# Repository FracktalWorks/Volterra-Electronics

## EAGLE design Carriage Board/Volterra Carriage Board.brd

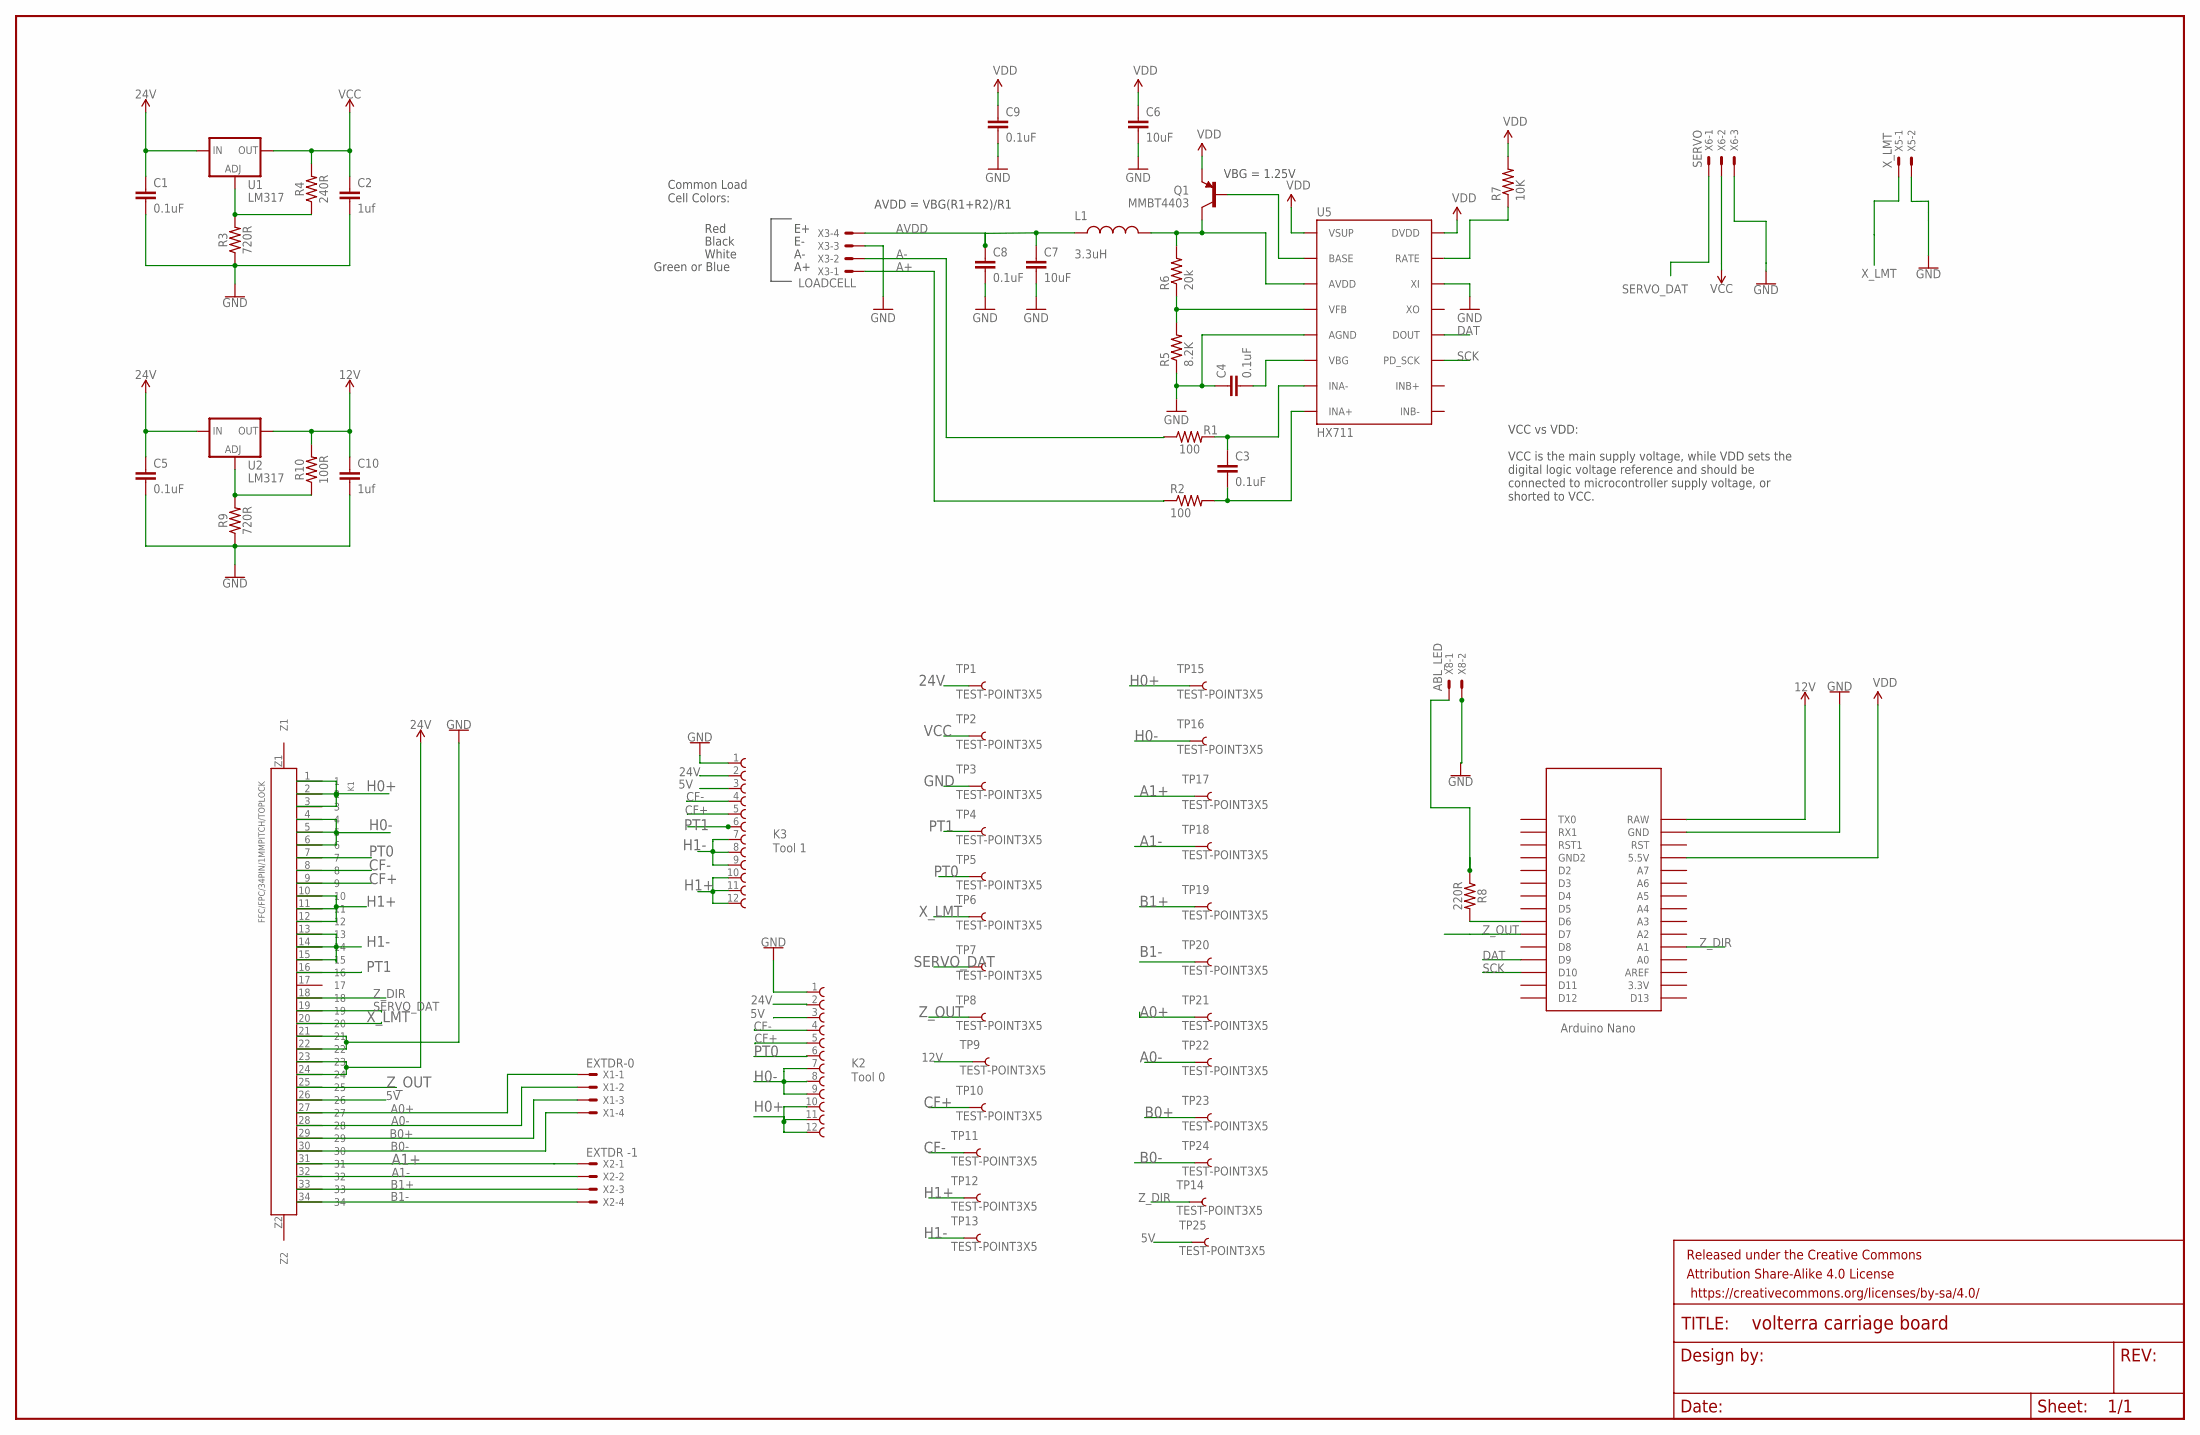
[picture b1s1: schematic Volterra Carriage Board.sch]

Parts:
C1, C5: 0.1uF; 0603
C2, C10: 1uf; 0603
C3, C4, C8, C9: 0.1uF; 0603-CAP
C6, C7: 10uF; 1210
FRAME1: FRAME-LEDGER; CREATIVE_COMMONS
K1: FFC/FPC/34PIN/1MMPITCH/TOPLOCK; 34PIN/1MMPITCH/FFC/FPC
K2: Tool 0; 68611214122
K3: Tool 1; 68611214122
L1: 3.3uH; 0805
Q1: MMBT4403; SOT23-3
R1, R2: 100; 0603-RES
R3, R9: 720R; 0603
R4: 240R; 0603
R5: 8.2K; 0603-RES
R6: 20k; 0603-RES
R7: 10K; 0603-RES
R8: 220R; 0603
R10: 100R; 0603
TP1, TP2, TP3, TP4, TP5, TP6, TP7, TP8, TP9, TP10, TP11, TP12, TP13, TP14, TP15, TP16, TP17, TP18, TP19, TP20, TP21, TP22, TP23, TP24, TP25: TEST-POINT3X5; PAD.03X.05
U1, U2: LM317; SOT223
U5: HX711; SO16
U$1: NANO
X1: EXTDR-0; JST-XH-04-PACKAGE-LONG-PAD
X2: EXTDR -1; JST-XH-04-PACKAGE-LONG-PAD
X3: LOADCELL; JST-XH-04-PACKAGE-LONG-PAD
X5: X_LMT; JST-XH-02-PACKAGE-LONG-PAD
X6: SERVO; JST-XH-03-PACKAGE-LONG-PAD
X8: ABL_LED; JST-XH-02-PACKAGE-LONG-PAD

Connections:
5V: K1.26, K2.3, K3.3, TP25.P$1
12V: C10.1, R10.2, TP9.P$1, U2.2 (OUT), U$1.RAW
24V: C1.1, C5.1, K1.23, K1.24, K2.2, K3.2, TP1.P$1, U1.3 (IN), U2.3 (IN)
A0+: K1.27, TP21.P$1, X1.1
A0-: K1.28, TP22.P$1, X1.2
A1+: K1.31, TP17.P$1, X2.1
A1-: K1.32, TP18.P$1, X2.2
A+: R2.1, X3.1
A-: R1.1, X3.2
ADJ: R3.2, R4.1, U1.1 (ADJ)
ADJ1: R9.2, R10.1, U2.1 (ADJ)
AVDD: C7.1, C8.1, L1.1, X3.4
B0+: K1.29, TP23.P$1, X1.3
B0-: K1.30, TP24.P$1, X1.4
B1+: K1.33, TP19.P$1, X2.3
B1-: K1.34, TP20.P$1, X2.4
CF+: K1.9, K2.5, K3.5, TP10.P$1
CF-: K1.8, K2.4, K3.4, TP11.P$1
DAT: U5.12 (DOUT), U$1.D9
GND: C1.2, C2.2, C4.1, C5.2, C6.2, C7.2, C8.2, C9.2, C10.2, K1.21, K1.22, K2.1, K3.1, R3.1, R5.1, R9.1, TP3.P$1, U5.5 (AGND), U5.14 (XI), U$1.GND, X3.3, X5.2, X6.3, X8.2
H0+: K1.1, K1.2, K1.3, K2.10, K2.11, K2.12, TP15.P$1
H0-: K1.4, K1.5, K1.6, K2.7, K2.8, K2.9, TP16.P$1
H1+: K1.10, K1.11, K1.12, K3.10, K3.11, K3.12, TP12.P$1
H1-: K1.13, K1.14, K1.15, K3.7, K3.8, K3.9, TP13.P$1
unnamed: R8.2, U$1.D6
unnamed: R7.1, U5.15 (RATE)
unnamed: C3.1, R1.2, U5.7 (INA-)
unnamed: Q1.1 (B), U5.2 (BASE)
unnamed: L1.2, Q1.3 (C), R6.2, U5.3 (AVDD)
unnamed: R5.2, R6.1, U5.4 (VFB)
unnamed: C4.2, U5.6 (VBG)
unnamed: C3.2, R2.2, U5.8 (INA+)
unnamed: R8.1, X8.1
PT0: K1.7, K2.6, TP5.P$1
PT1: K1.16, K3.6, TP4.P$1
SCK: U5.11 (PD_SCK), U$1.D10
SERVO_DAT: K1.19, TP7.P$1, X6.1
VCC: C2.1, R4.2, TP2.P$1, U1.2 (OUT), X6.2
VDD: C6.1, C9.1, Q1.2 (E), R7.2, U5.1 (VSUP), U5.16 (DVDD), U$1.5V (5.5V)
X_LMT: K1.20, TP6.P$1, X5.1
Z_DIR: K1.18, TP14.P$1, U$1.A1
Z_OUT: K1.25, TP8.P$1, U$1.D7

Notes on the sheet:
VBG = 1.25V
AVDD = VBG(R1+R2)/R1
Red
Black
White
Green or Blue
Common Load Cell Colors:
VCC vs VDD: VCC is the main supply voltage, while VDD sets the digital logic voltage reference and should be connected to microcontroller supply voltage, or shorted to VCC.

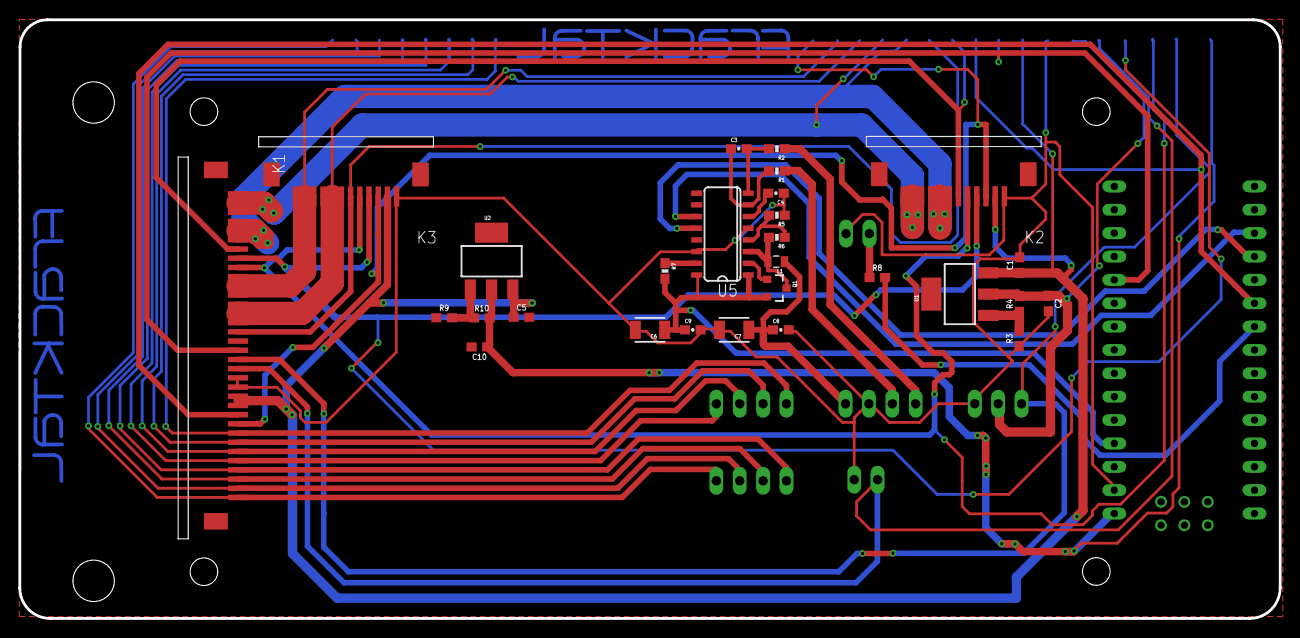
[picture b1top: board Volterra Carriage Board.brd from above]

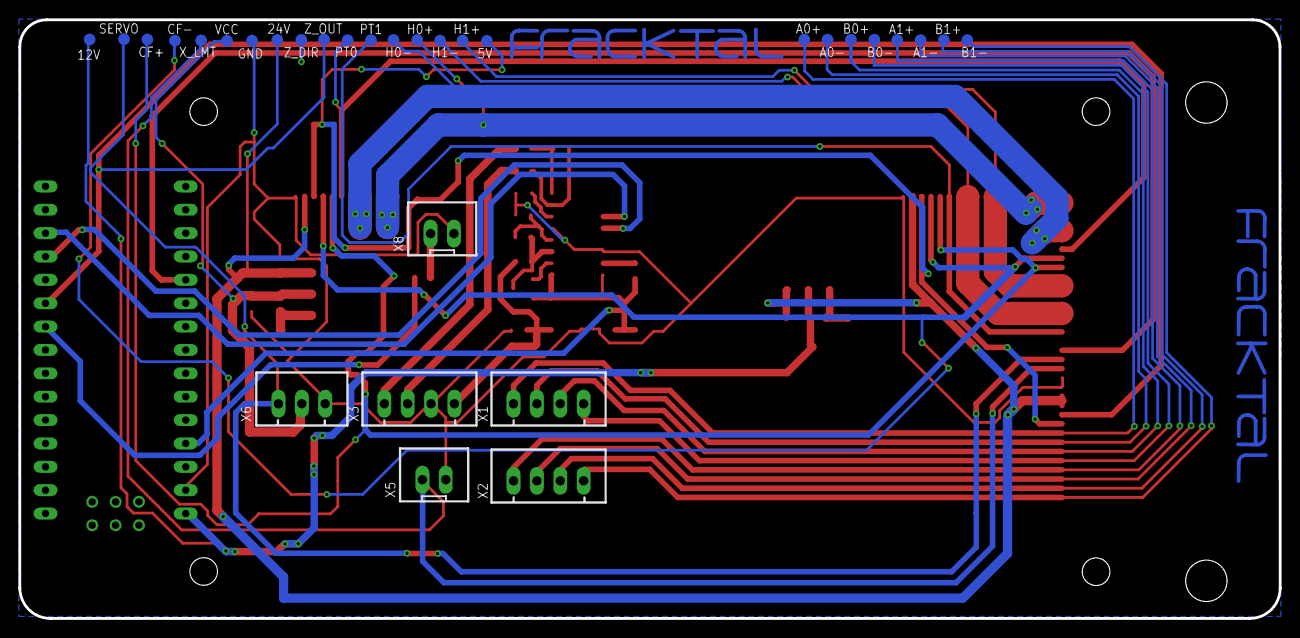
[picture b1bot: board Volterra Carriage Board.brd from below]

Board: 2 copper layers, 137.0 x 65.1 mm, 63 parts (33 on the bottom side), 42 nets.

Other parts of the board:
U$2, U$3: FRACKTALLOGO

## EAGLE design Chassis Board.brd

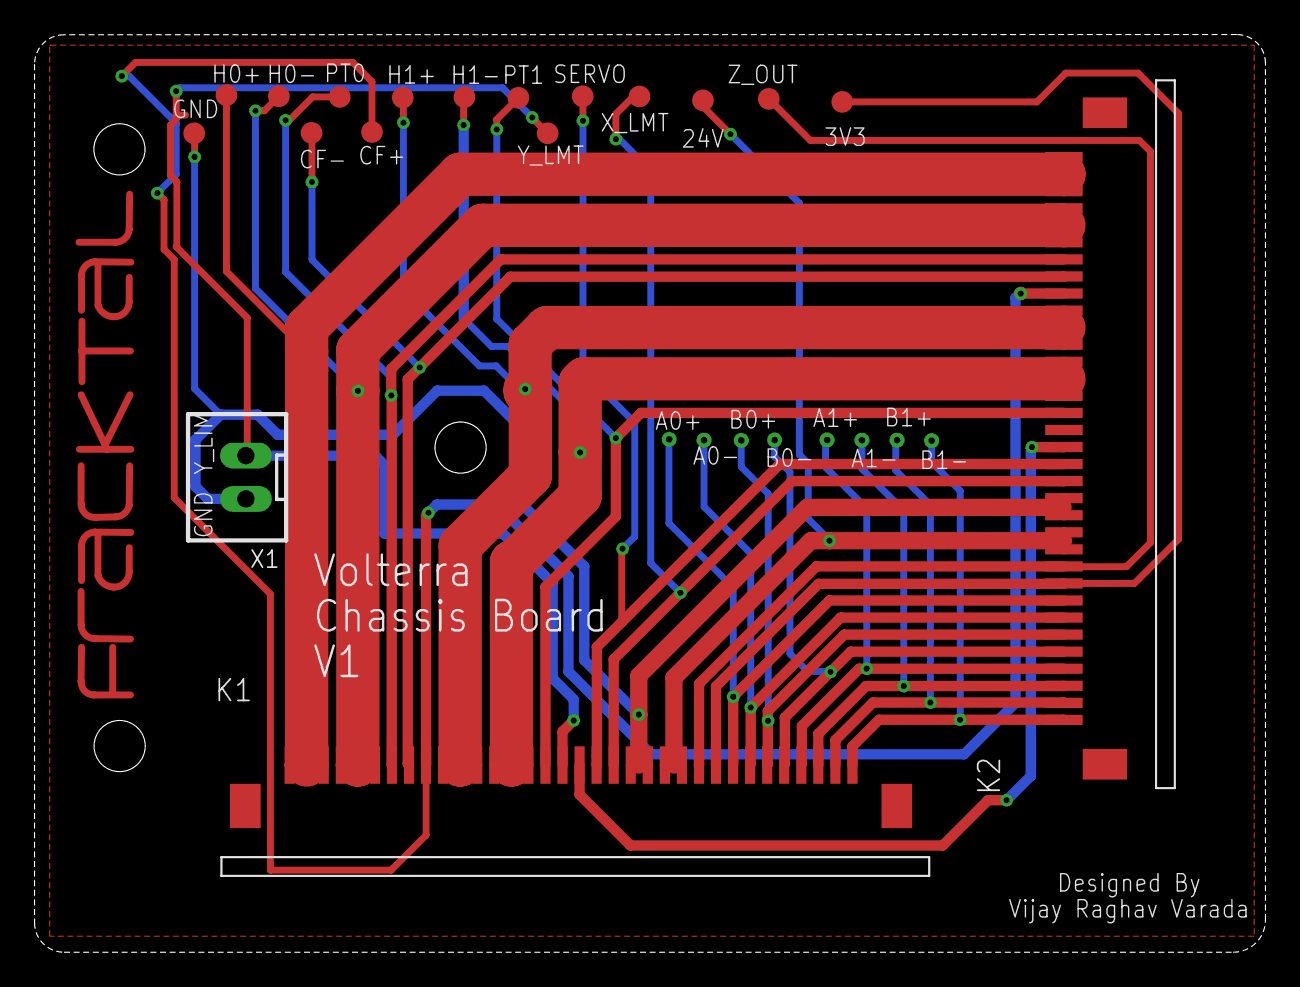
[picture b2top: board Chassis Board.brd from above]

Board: 2 copper layers, 72.2 x 53.8 mm, 27 parts (0 on the bottom side), 24 nets.

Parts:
K1, K2: FFC/FPC/34PIN/1MMPITCH/TOPLOCK; 34PIN/1MMPITCH/FFC/FPC
TP1, TP2, TP3, TP4, TP5, TP6, TP7, TP8, TP9, TP10, TP11, TP12, TP13, TP14, TP23: TEST-POINT3X5; PAD.03X.05
TP15, TP16, TP17, TP18, TP19, TP20, TP21, TP22: TEST-POINTTP_15TH_THRU; TP_15TH
U$1: FRACKTALLOGO
X1: Y_LMT; JST-XH-02-PACKAGE-LONG-PAD

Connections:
3V3: K1.26, K2.9, TP9.P$1
24V: K1.23, K1.24, K2.11, K2.12, TP12.P$1
A0+: K1.27, K2.8, TP15.P$1
A0-: K1.28, K2.7, TP16.P$1
A1+: K1.31, K2.4, TP19.P$1
A1-: K1.32, K2.3, TP20.P$1
B0+: K1.29, K2.6, TP17.P$1
B0-: K1.30, K2.5, TP18.P$1
B1+: K1.33, K2.2, TP21.P$1
B1-: K1.34, K2.1, TP22.P$1
CF+: K1.9, K2.26, TP7.P$1
CF-: K1.8, K2.27, TP6.P$1
GND: K1.21, K1.22, K2.13, K2.14, TP13.P$1, X1.1
H0+: K1.1, K1.2, K1.3, K2.32, K2.33, K2.34, TP1.P$1
H0-: K1.4, K1.5, K1.6, K2.29, K2.30, K2.31, TP2.P$1
H1+: K1.10, K1.11, K1.12, K2.23, K2.24, K2.25, TP4.P$1
H1-: K1.13, K1.14, K1.15, K2.20, K2.21, K2.22, TP5.P$1
PT0: K1.7, K2.28, TP3.P$1
PT1: K1.16, K2.19, TP23.P$1
SERVO_DAT: K1.19, K2.16, TP14.P$1
X_LMT: K1.20, K2.15, TP10.P$1
Y_LMT: K1.17, TP11.P$1, X1.2
Z_DIR: K1.18, K2.17
Z_OUT: K1.25, K2.10, TP8.P$1

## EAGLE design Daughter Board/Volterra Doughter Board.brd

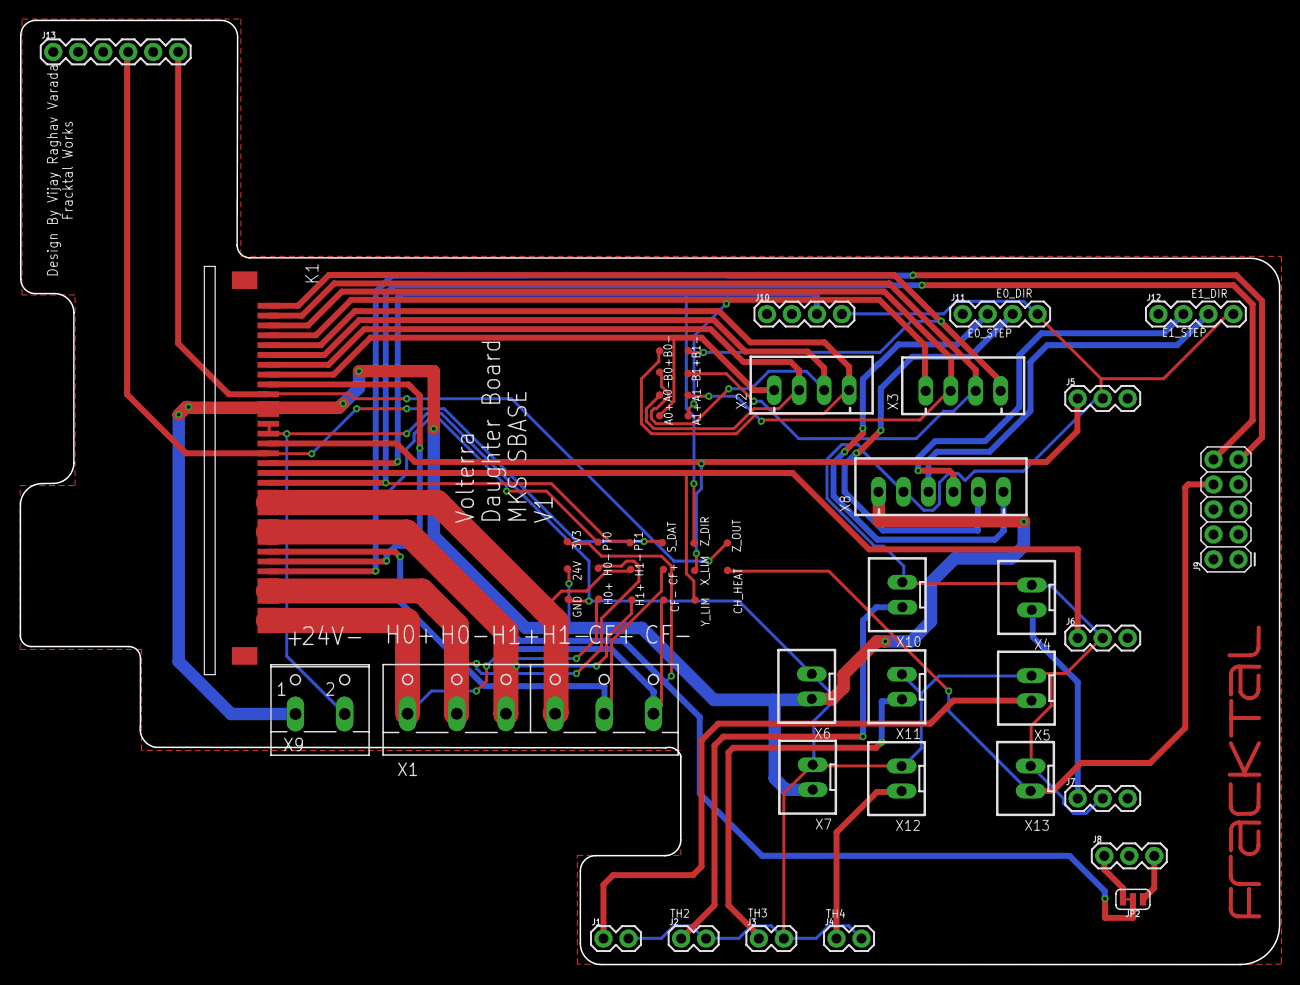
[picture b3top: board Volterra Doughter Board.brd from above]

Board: 2 copper layers, 128.0 x 96.0 mm, 55 parts (0 on the bottom side), 36 nets.

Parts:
FRAME1: FRAME-LEDGER; CREATIVE_COMMONS
J1, J2, J3, J4: 1X02
J5, J6, J7, J8: 455-1750-1-ND; 1X03
J9: 2X5
J10, J11, J12: 1X04
J13: 1X06
JP2: 3V3/5 SEL; SMT-JUMPER_3_1-NC_TRACE_SILK
K1: FFC/FPC/34PIN/1MMPITCH/TOPLOCK; 34PIN/1MMPITCH/FFC/FPC
TP1, TP2, TP3, TP4, TP5, TP6, TP7, TP8, TP9, TP10, TP11, TP12, TP13, TP14, TP15, TP16, TP17, TP18, TP19, TP20, TP21, TP22, TP23, TP24, TP25: TEST-POINT3; PAD.03X.03
U$1: FRACKTALLOGO
X1: W237-6
X2: EXTDR-0; JST-XH-04-PACKAGE-LONG-PAD
X3: EXTDR-1; JST-XH-04-PACKAGE-LONG-PAD
X4: Z_LMT; JST-XH-02-PACKAGE-LONG-PAD
X5: BED_THERM; JST-XH-02-PACKAGE-LONG-PAD
X6, X7: 24V; JST-XH-02-PACKAGE-LONG-PAD
X8: FILAMENT SENSOR; JST-XH-06-PACKAGE-LONG-PAD
X9: W237-102
X10: TH4; JST-XH-02-PACKAGE-LONG-PAD
X11: TH3; JST-XH-02-PACKAGE-LONG-PAD
X12: TH2; JST-XH-02-PACKAGE-LONG-PAD
X13: CH_HEAT; JST-XH-02-PACKAGE-LONG-PAD

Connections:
3V3: JP2.2, K1.9, TP24.P$1
24V: K1.11, K1.12, TP10.P$1, X6.1, X7.1, X8.1, X9.1
A0+: K1.8, TP8.P$1, X2.1
A0-: K1.7, TP7.P$1, X2.2
A1+: K1.4, TP4.P$1, X3.1
A1-: K1.3, TP3.P$1, X3.2
B0+: K1.6, TP6.P$1, X2.3
B0-: K1.5, TP5.P$1, X2.4
B1+: K1.2, TP2.P$1, X3.3
B1-: K1.1, TP1.P$1, X3.4
BED_THERM: J1.1, X5.1
CF+: K1.26, TP19.P$1, X1.5
CF-: K1.27, TP20.P$1, X1.6
CH_HEAT: J9.8, TP25.P$1, X13.1
E0_DIR: J11.3, X8.5
E0_STEP: J11.2, X8.6
E1_DIR: J12.3, X8.3
E1_STEP: J12.2, X8.4
GND: J1.2, J2.2, J3.2, J4.2, J5.2, J6.2, J7.2, J10.4, J11.4, J12.4, K1.13, K1.14, TP11.P$1, X4.2, X5.2, X6.2, X7.2, X8.2, X9.2, X10.2, X11.2, X12.2, X13.2
H0+: K1.32, K1.33, K1.34, TP23.P$1, X1.1
H0-: K1.29, K1.30, K1.31, TP22.P$1, X1.2
H1+: K1.23, K1.24, K1.25, TP18.P$1, X1.3
H1-: K1.20, K1.21, K1.22, TP17.P$1, X1.4
unnamed: J8.1, JP2.3
unnamed: J8.3, JP2.1
PT0: J9.9, K1.28, TP21.P$1
PT1: J9.10, K1.19, TP16.P$1
SERVO_DAT: J13.4, K1.16, TP13.P$1
TH2: J2.1, X10.1
TH3: J3.1, X11.1
TH4: J4.1, X12.1
X_LMT: J5.1, K1.15, TP12.P$1
Y_LMT: J6.1, K1.18, TP15.P$1
Z_DIR: J10.3, K1.17, TP14.P$1
Z_LMT: J7.1, X4.1
Z_OUT: J13.6, K1.10, TP9.P$1

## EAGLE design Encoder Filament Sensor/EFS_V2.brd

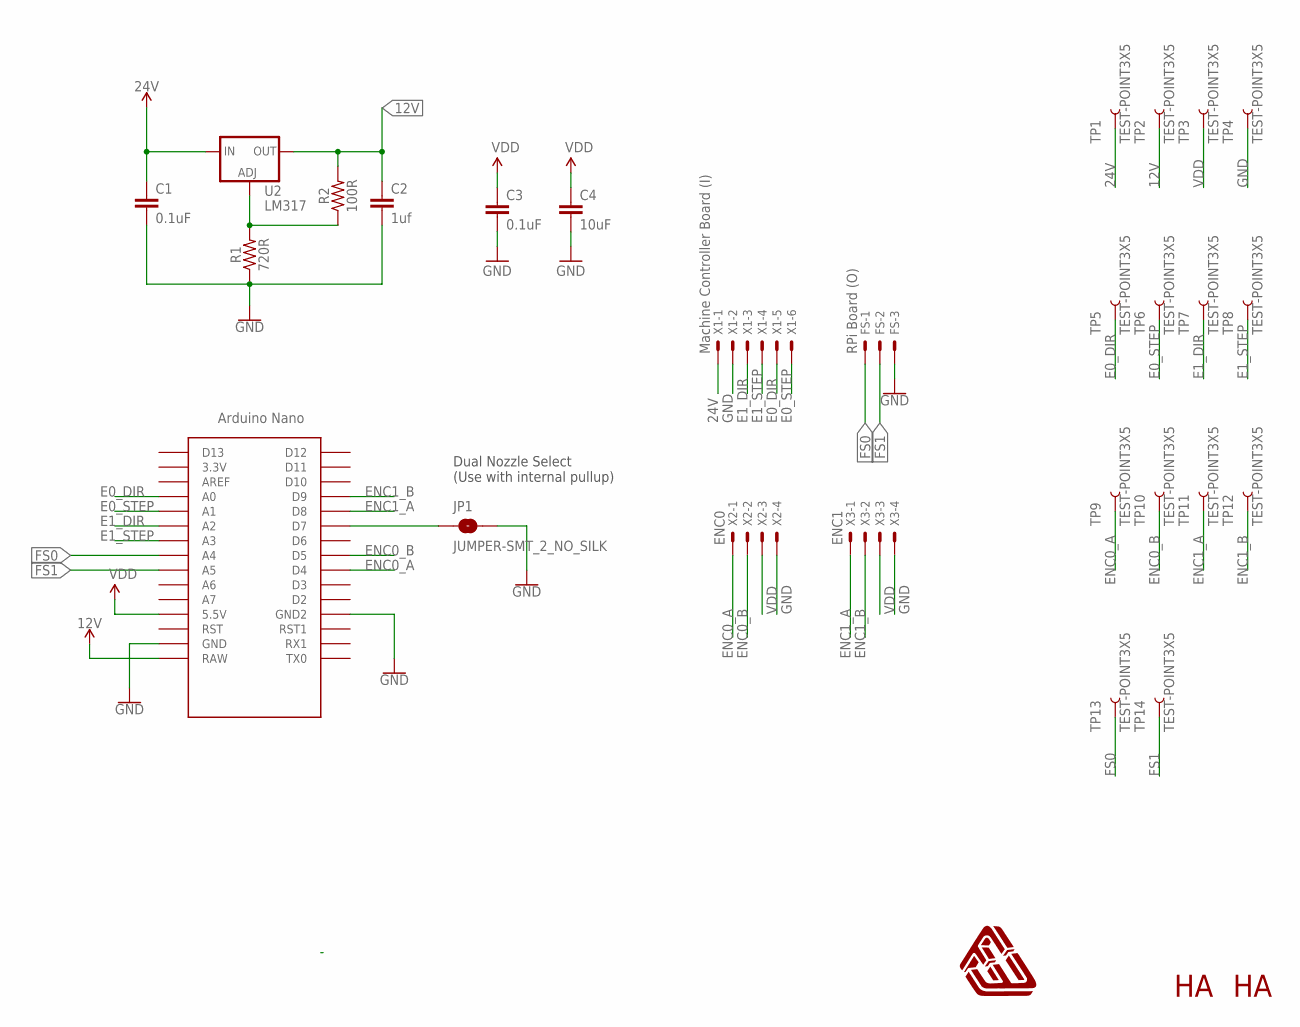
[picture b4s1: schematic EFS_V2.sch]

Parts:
C1: 0.1uF; 0603
C2: 1uf; 0603
C3: 0.1uF; 0603-CAP
C4: 10uF; 1210
FS: RPi Board (O); JST-XH-03-PACKAGE-LONG-PAD
JP1: JUMPER-SMT_2_NO_SILK; SMT-JUMPER_2_NO_SILK
M_HA_1, M_HA_2: HA_MARK
R1: 720R; 0603
R2: 100R; 0603
TP1, TP2, TP3, TP4, TP5, TP6, TP7, TP8, TP9, TP10, TP11, TP12, TP13, TP14: TEST-POINT3X5; PAD.03X.05
U2: LM317; SOT223
U$1: NANO
U$2: FWLOGO
X1: Machine Controller Board (I); JST-XH-06-PACKAGE-LONG-PAD
X2: ENC0; JST-XH-04-PACKAGE-LONG-PAD
X3: ENC1; JST-XH-04-PACKAGE-LONG-PAD

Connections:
12V: C2.1, R2.2, TP2.P$1, U2.2 (OUT), U$1.RAW
24V: C1.1, TP1.P$1, U2.3 (IN), X1.1
ADJ1: R1.2, R2.1, U2.1 (ADJ)
E0_DIR: TP5.P$1, U$1.A0, X1.5
E0_STEP: TP6.P$1, U$1.A1, X1.6
E1_DIR: TP7.P$1, U$1.A2, X1.3
E1_STEP: TP8.P$1, U$1.A3, X1.4
ENC0_A: TP9.P$1, U$1.D4, X2.1
ENC0_B: TP10.P$1, U$1.D5, X2.2
ENC1_A: TP11.P$1, U$1.D8, X3.1
ENC1_B: TP12.P$1, U$1.D9, X3.2
FS0: FS.1, TP13.P$1, U$1.A4
FS1: FS.2, TP14.P$1, U$1.A5
GND: C1.2, C2.2, C3.2, C4.2, FS.3, JP1.2, R1.1, TP4.P$1, U$1.GND, U$1.GND1 (GND2), X1.2, X2.4, X3.4
unnamed: JP1.1, U$1.D7
VDD: C3.1, C4.1, TP3.P$1, U$1.5V (5.5V), X2.3, X3.3

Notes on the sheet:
Dual Nozzle Select (Use with internal pullup)

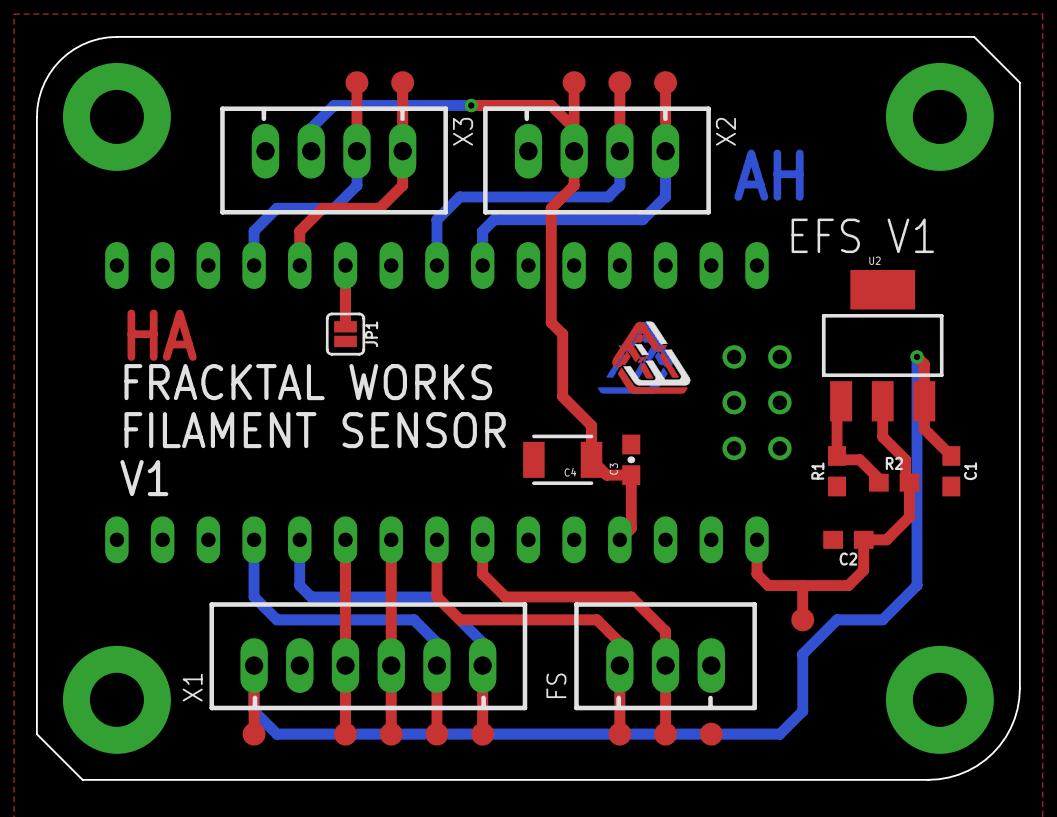
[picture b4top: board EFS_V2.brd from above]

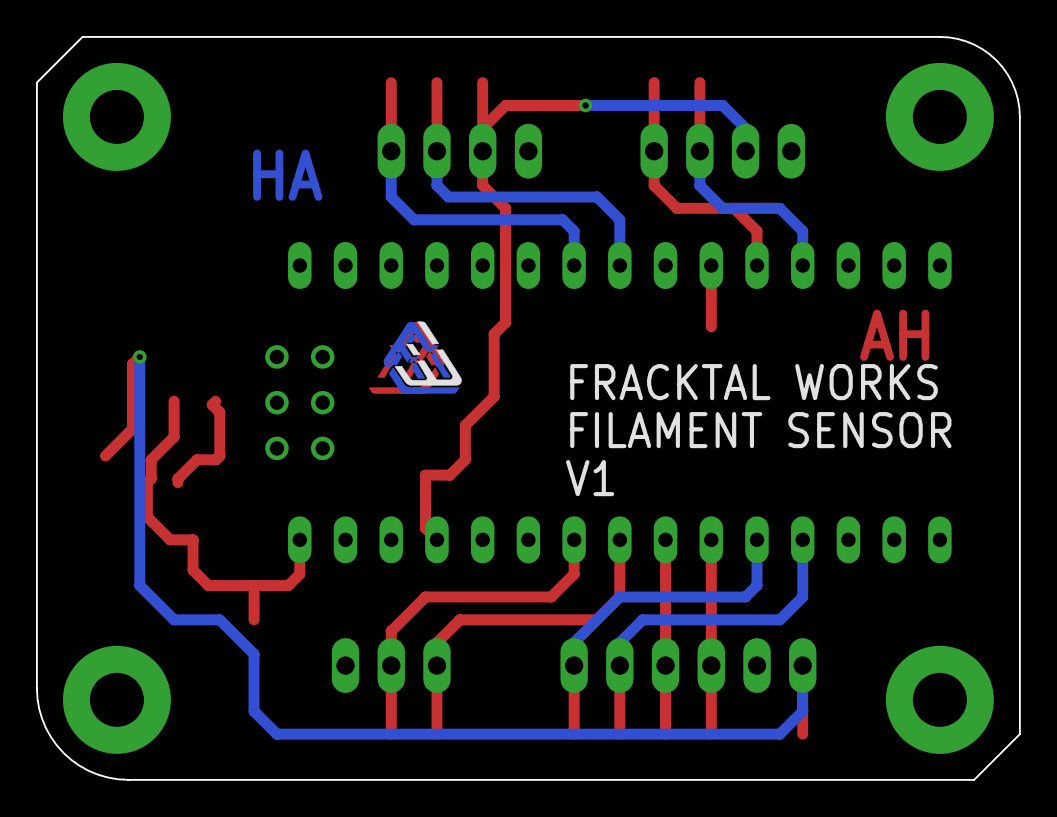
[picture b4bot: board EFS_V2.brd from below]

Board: 2 copper layers, 54.6 x 41.3 mm, 31 parts (2 on the bottom side), 16 nets.

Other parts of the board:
U$4: FWLOGO

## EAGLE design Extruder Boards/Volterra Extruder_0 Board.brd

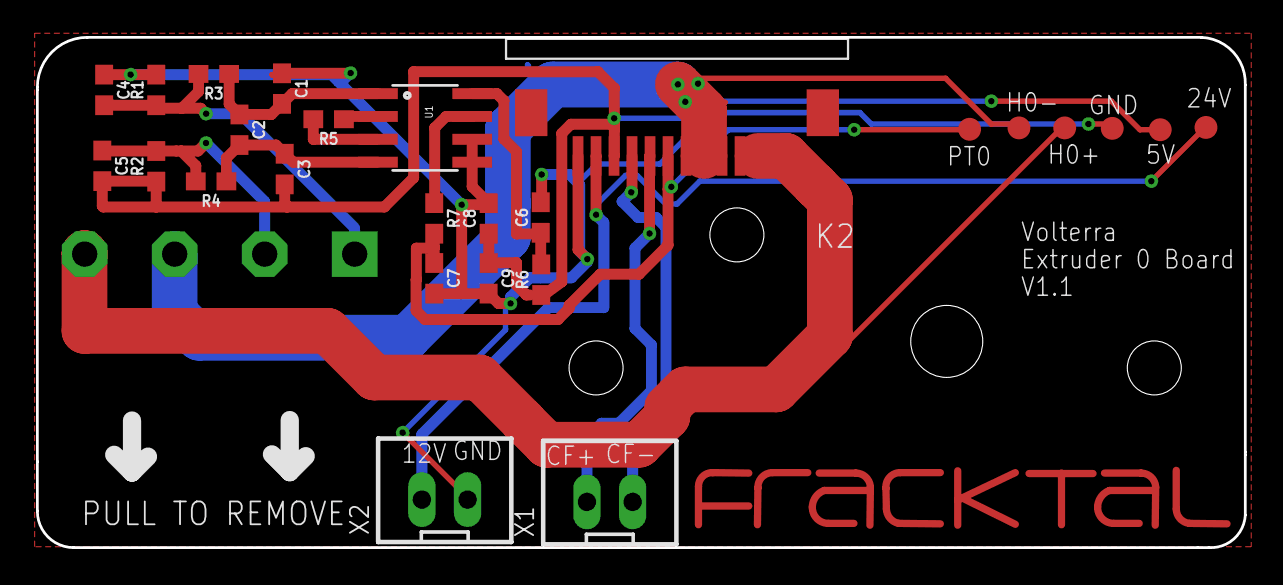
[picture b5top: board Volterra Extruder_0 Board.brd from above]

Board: 2 copper layers, 67.1 x 28.3 mm, 28 parts (1 on the bottom side), 16 nets.

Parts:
C1, C3, C4, C5, C6: 100nF; 0603
C2: 1uF; 0603
C7: 10nF; 0603
C8, C9: 10uF; 0603
J1: TERMINALBLOCK/4PIN/5MMPITCH; TERMINALBLOCK/TOYO/4PIN/5MMPITCH
K2: 68611214122
R1, R2: 2.2k; 0603
R3, R4: 10k; 0603
R5: 5.49k; 0603
R6, R7: 100R; 0603
TP1, TP2, TP5, TP6, TP7, TP8: TEST-POINT3X5; PAD.03X.05
U1: INA826SOIC-08; SOIC-8
U$1: FRACKTALLOGO
X1: CF; JST-XH-02-PACKAGE-LONG-PAD
X2: AOF; JST-XH-02-PACKAGE-LONG-PAD

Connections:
5V: C3.2, C5.2, C8.1, C9.1, K2.10, R2.1, R6.1, TP8.P$1
24V: K2.11, TP6.P$1, X2.1
CF+: K2.8, X1.1
CF-: K2.9, X1.2
GND: C1.1, C4.1, C6.2, C7.2, C8.2, C9.2, K2.12, R1.2, TP7.P$1, U1.5, U1.6, X2.2
H0+: J1.4, K2.1, K2.2, K2.3, TP1.P$1
H0-: J1.3, K2.4, K2.5, K2.6, TP2.P$1
IN+: C5.1, J1.2, R2.2, R4.2
IN-: C4.2, J1.1, R1.1, R3.2
unnamed: R5.1, U1.2
unnamed: R5.2, U1.3
unnamed: C1.2, C2.1, R3.1, U1.1
unnamed: C2.2, C3.1, R4.1, U1.4
unnamed: C6.1, R6.2, U1.8
unnamed: R7.1, U1.7
PT0: C7.1, K2.7, R7.2, TP5.P$1

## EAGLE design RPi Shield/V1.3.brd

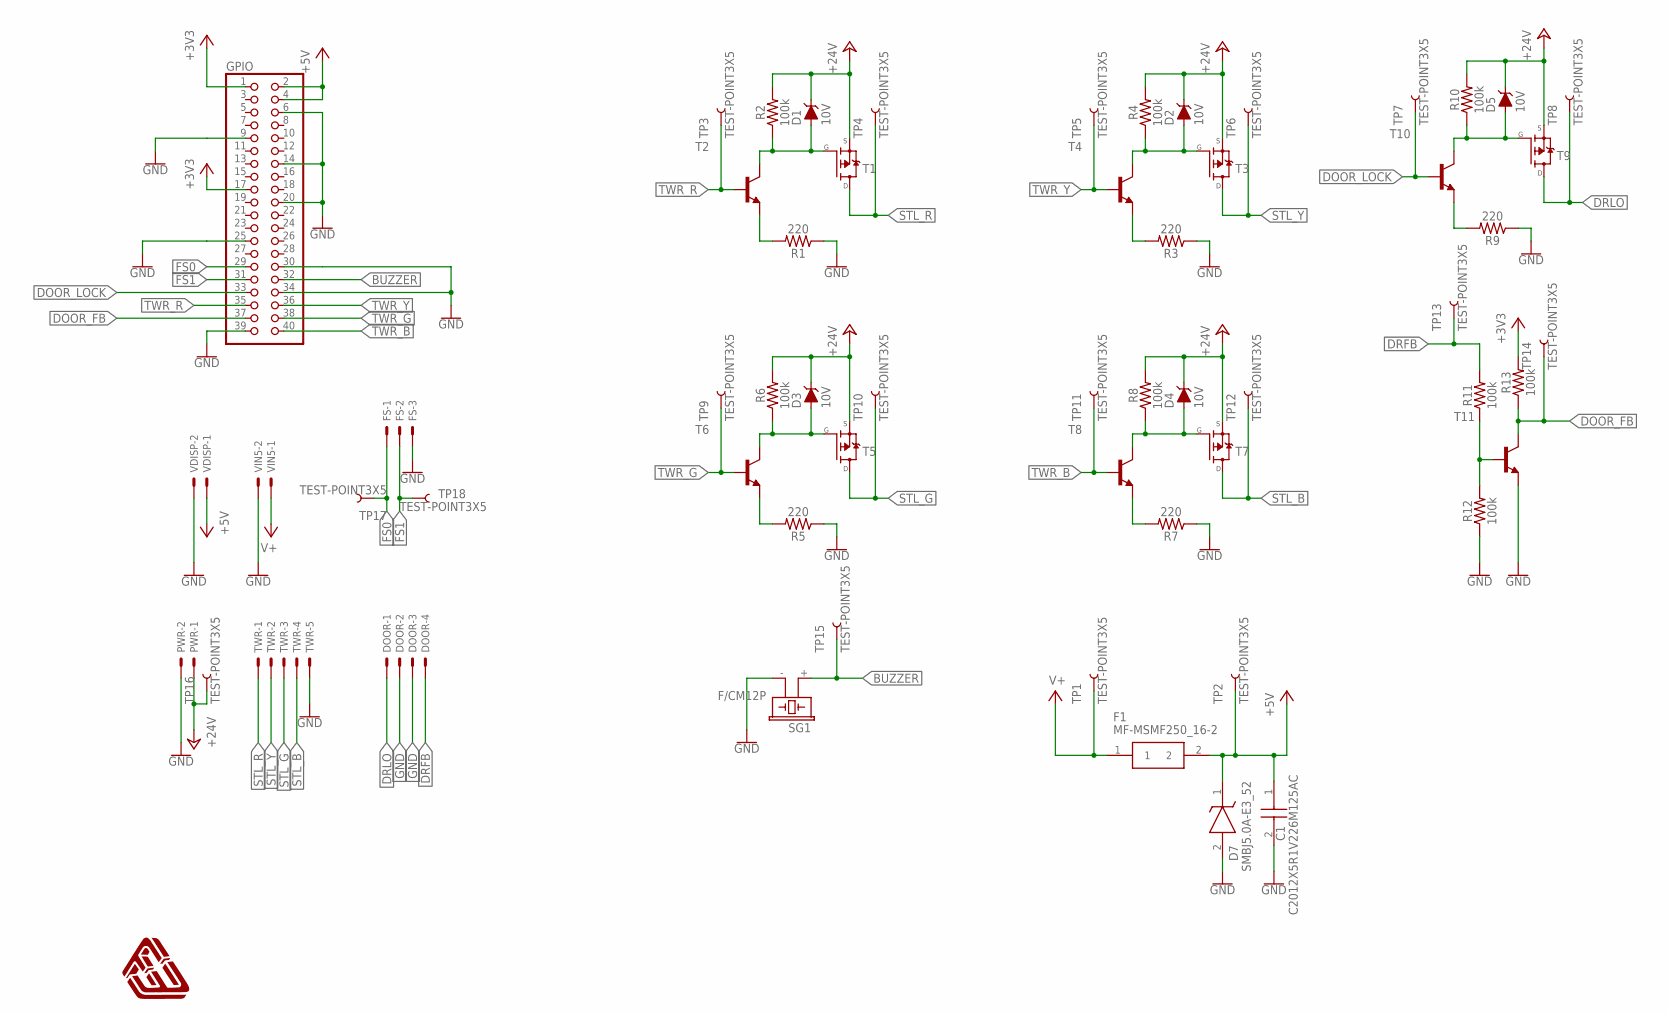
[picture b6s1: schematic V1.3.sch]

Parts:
C1: C2012X5R1V226M125AC; CAPC2012X145N
D1, D2, D3, D4, D5: 10V; PANASONIC_SMINI2-F5-B
D7: SMBJ5.0A-E3_52; DIOM5436X244N
DOOR: JST-XH-04-PIN-LONG-PAD; JST-XH-04-PACKAGE-LONG-PAD
F1: MF-MSMF250_16-2; FUSC4632X160N
FS: JST-XH-03-PIN-LONG-PAD; JST-XH-03-PACKAGE-LONG-PAD
GPIO: RASPBERRYPI_3B_GPIO
PWR: JST-XH-02-PIN-LONG-PAD; JST-XH-02-PACKAGE-LONG-PAD
R1, R3, R5, R7, R9: 220; 0603
R2, R4, R6, R8, R10, R11, R12, R13: 100k; 0603
SG1: F/CM12P
T1, T3, T5, T7, T9: MOSFET_P_SOT223; MOSFET_SOT223
T2, T4, T6, T8, T10, T11: MMBT3904LT1-NPN-SOT23-BEC; SOT23-BEC
TP1, TP2, TP3, TP4, TP5, TP6, TP7, TP8, TP9, TP10, TP11, TP12, TP13, TP14, TP15, TP16, TP17, TP18: TEST-POINT3X5; PAD.03X.05
TWR: JST-XH-05-PIN-LONG-PAD; JST-XH-05-PACKAGE-LONG-PAD
U$5: FWLOGO
VDISP: JST-XH-02-PIN-LONG-PAD; JST-XH-02-PACKAGE-LONG-PAD
VIN5: JST-XH-02-PIN-LONG-PAD; JST-XH-02-PACKAGE-LONG-PAD

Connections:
+3V3: GPIO.1, GPIO.17, R13.2
+5V: C1.1, D7.1 (K), F1.2, GPIO.2, GPIO.4, TP2.P$1, VDISP.1
+24V: D1.C, D2.C, D3.C, D4.C, D5.C, PWR.1, R2.2, R4.2, R6.2, R8.2, R10.2, T1.3 (S), T3.3 (S), T5.3 (S), T7.3 (S), T9.3 (S), TP16.P$1
BUZZER: GPIO.32, SG1.+ (1), TP15.P$1
DOOR_FB: GPIO.37, R13.1, T11.C, TP14.P$1
DOOR_LOCK: GPIO.33, T10.B, TP7.P$1
DRFB: DOOR.4, R11.2, TP13.P$1
DRLO: DOOR.1, T9.2 (D), T9.4 (D), TP8.P$1
FS0: FS.1, GPIO.29, TP17.P$1
FS1: FS.2, GPIO.31, TP18.P$1
GND: C1.2, D7.2 (A), DOOR.2, DOOR.3, FS.3, GPIO.6, GPIO.9, GPIO.14, GPIO.20, GPIO.25, GPIO.30, GPIO.34, GPIO.39, PWR.2, R1.1, R3.1, R5.1, R7.1, R9.1, R12.1, SG1.- (2), T11.E, TWR.5, VDISP.2, VIN5.2
unnamed: R1.2, T2.E
unnamed: D2.A, R4.1, T3.1 (G), T4.C
unnamed: D1.A, R2.1, T1.1 (G), T2.C
unnamed: R11.1, R12.2, T11.B
unnamed: R3.2, T4.E
unnamed: D3.A, R6.1, T5.1 (G), T6.C
unnamed: R5.2, T6.E
unnamed: D4.A, R8.1, T7.1 (G), T8.C
unnamed: R7.2, T8.E
unnamed: D5.A, R10.1, T9.1 (G), T10.C
unnamed: R9.2, T10.E
STL_B: T7.2 (D), T7.4 (D), TP12.P$1, TWR.4
STL_G: T5.2 (D), T5.4 (D), TP10.P$1, TWR.3
STL_R: T1.2 (D), T1.4 (D), TP4.P$1, TWR.1
STL_Y: T3.2 (D), T3.4 (D), TP6.P$1, TWR.2
TWR_B: GPIO.40, T8.B, TP11.P$1
TWR_G: GPIO.38, T6.B, TP9.P$1
TWR_R: GPIO.35, T2.B, TP3.P$1
TWR_Y: GPIO.36, T4.B, TP5.P$1
V+: F1.1, TP1.P$1, VIN5.1

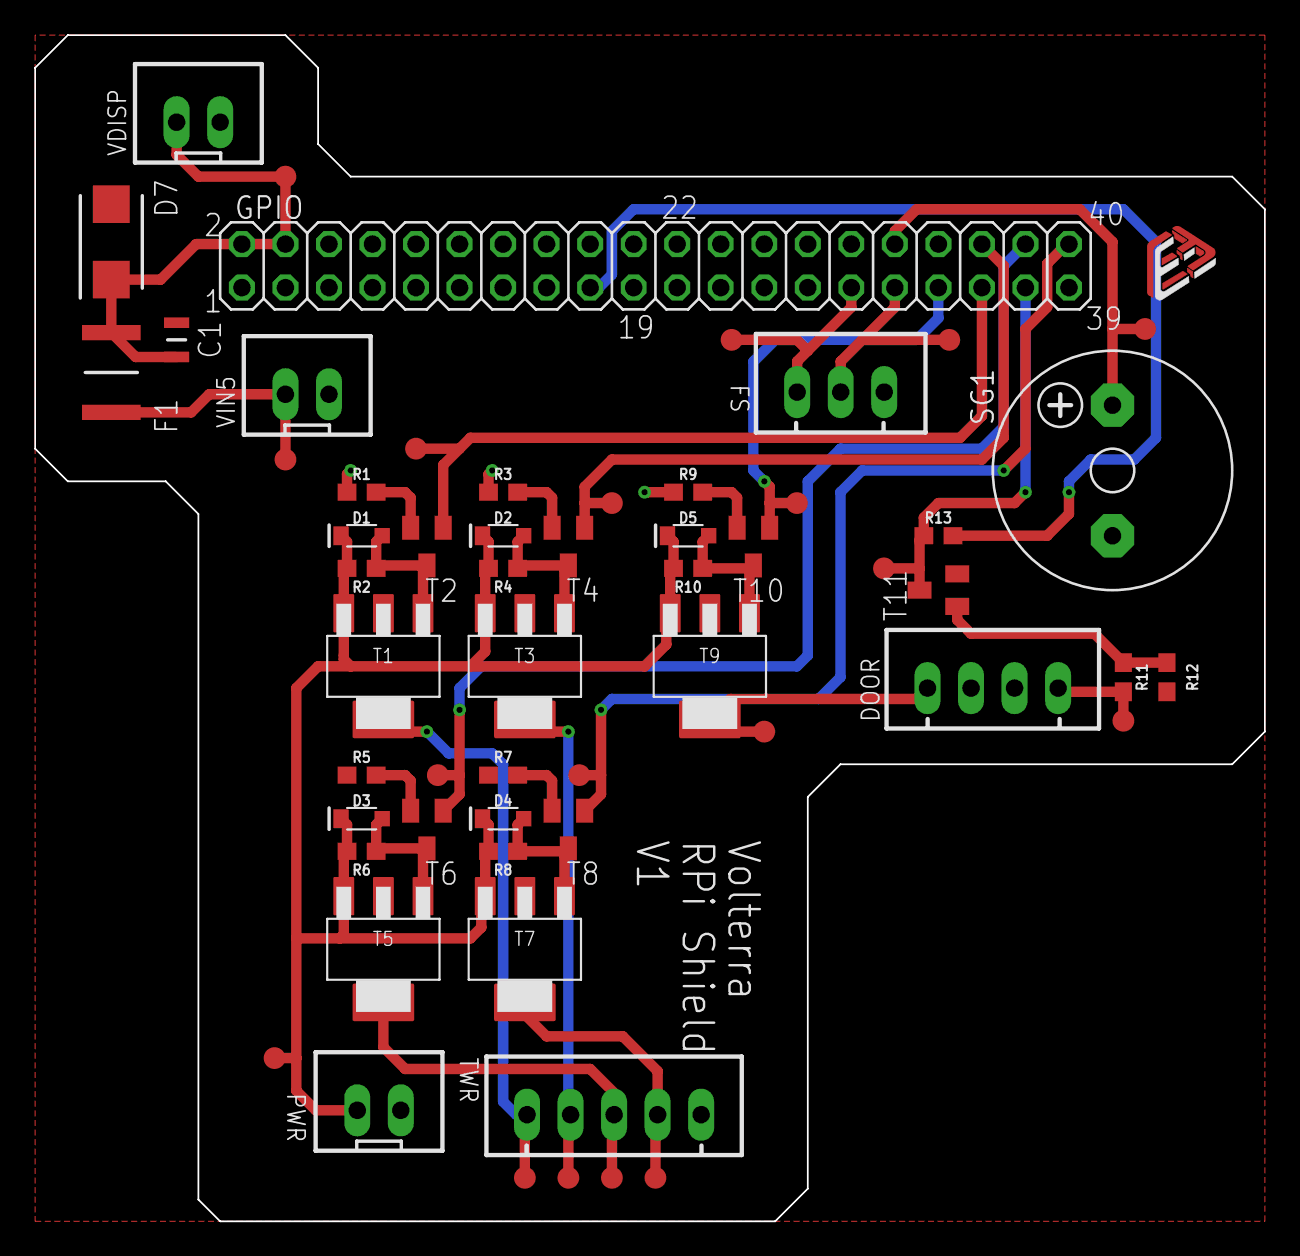
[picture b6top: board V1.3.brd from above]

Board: 2 copper layers, 71.8 x 69.2 mm, 59 parts (0 on the bottom side), 31 nets.

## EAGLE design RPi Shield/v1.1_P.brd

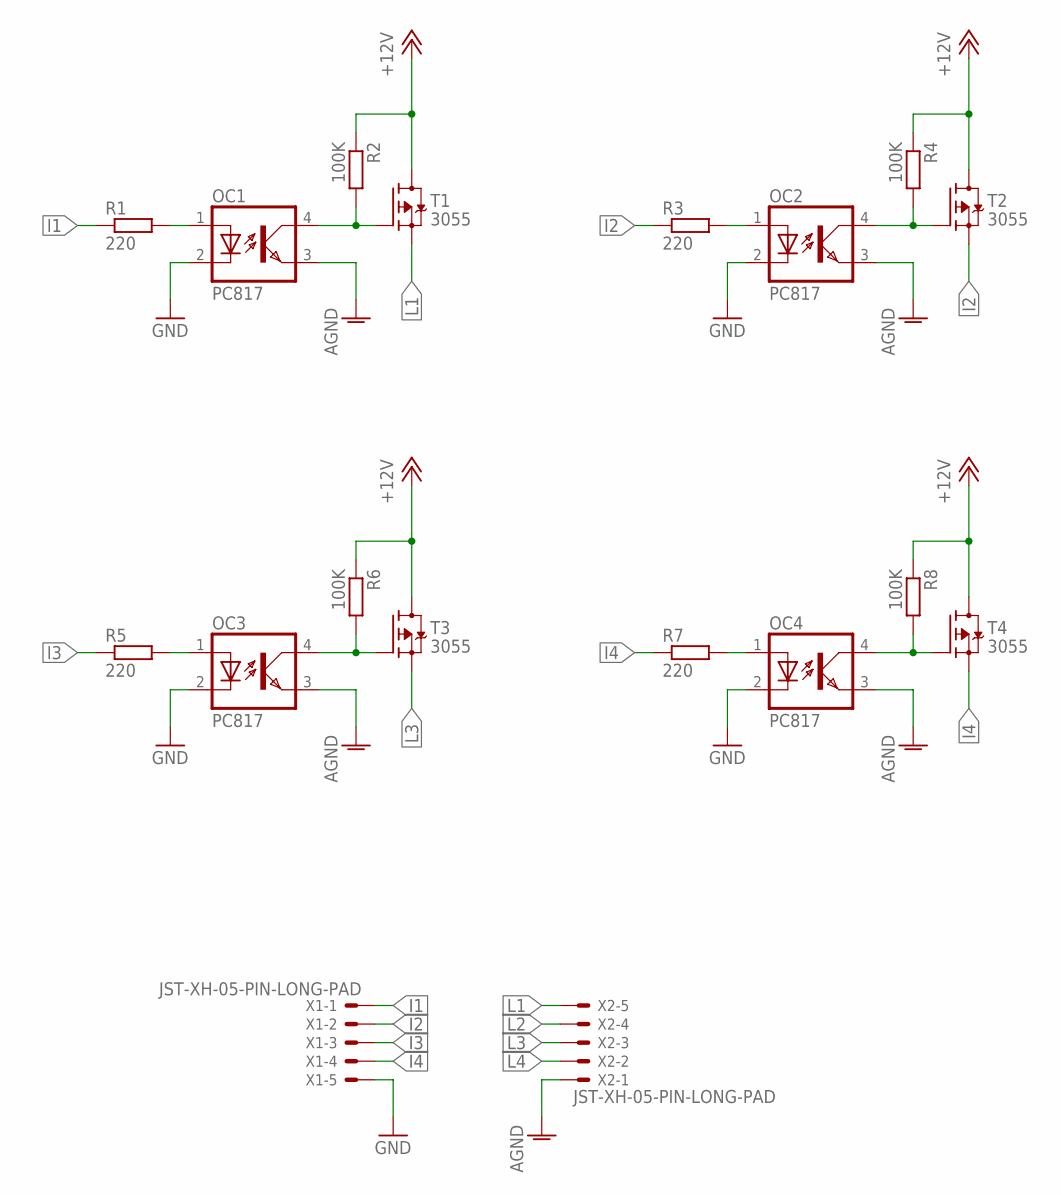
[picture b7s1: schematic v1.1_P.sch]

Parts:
OC1, OC2, OC3, OC4: PC817; DIL04
R1, R3, R5, R7: 220; R0603
R2, R4, R6, R8: 100K; R0603
T1, T2, T3, T4: 3055; MOSFET_P_SOT223
X1, X2: JST-XH-05-PIN-LONG-PAD; JST-XH-05-PACKAGE-LONG-PAD

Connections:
+12V: R2.1, R4.1, R6.1, R8.1, T1.2 (D), T1.4 (D), T2.2 (D), T2.4 (D), T3.2 (D), T3.4 (D), T4.2 (D), T4.4 (D)
AGND: OC1.3 (EMIT), OC2.3 (EMIT), OC3.3 (EMIT), OC4.3 (EMIT), X2.1
GND: OC1.2 (C), OC2.2 (C), OC3.2 (C), OC4.2 (C), X1.5
I1: R1.1, X1.1
I2: R3.1, T2.3 (S), X1.2
I3: R5.1, X1.3
I4: R7.1, T4.3 (S), X1.4
L1: T1.3 (S), X2.5
L2: X2.4
L3: T3.3 (S), X2.3
L4: X2.2
unnamed: OC1.1 (A), R1.2
unnamed: OC1.4 (COL), R2.2, T1.1 (G)
unnamed: OC2.1 (A), R3.2
unnamed: OC2.4 (COL), R4.2, T2.1 (G)
unnamed: OC3.1 (A), R5.2
unnamed: OC3.4 (COL), R6.2, T3.1 (G)
unnamed: OC4.1 (A), R7.2
unnamed: OC4.4 (COL), R8.2, T4.1 (G)

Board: 2 copper layers, 18 parts (0 on the bottom side), 17 nets, no tracks yet.

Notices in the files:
parts and their libraries:
SparkFun-Capacitors: Licensing: Creative Commons ShareAlike 4.0 International - https://creativecommons.org/licenses/by-sa/4.0
SparkFun-Aesthetics: Released under the Creative Commons Attribution Share-Alike 4.0 License
SparkFun-Aesthetics: https://creativecommons.org/licenses/by-sa/4.0
